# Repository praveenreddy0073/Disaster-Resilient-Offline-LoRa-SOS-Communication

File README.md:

# Earthquake Emergency SOS Communication System

## Overview

India experiences frequent earthquakes that can damage cellular towers and disrupt internet connectivity. During such emergencies, victims may be unable to communicate their location to rescue teams.

This project provides an infrastructure-independent emergency communication system using ESP32 and LoRa (SX1278) technology. The system enables users to transmit SOS alerts and GPS coordinates over long distances even when conventional communication networks fail.

## Problem Statement

During major earthquakes:

- Cellular towers may become unavailable
- Internet connectivity can be disrupted
- Victims cannot easily communicate their location
- Rescue teams face delays in locating survivors

This project addresses these challenges through a long-range wireless communication network.

## Proposed Solution

The system consists of:

Mobile App
↓
ESP32 User Node
↓
LoRa Communication
↓
Relay Node
↓
Base Station
↓
Rescue Team

The user sends an SOS request through a mobile application. The ESP32 User Node receives the request and forwards it using LoRa technology. Relay Nodes extend coverage and the Base Station receives the alert and displays victim information.

## Key Features

- Long-range communication up to 15 km (Line of Sight)
- GPS-based location sharing
- Infrastructure-independent operation
- Low-power communication
- Emergency SOS transmission
- Relay-based message forwarding
- Rescue acknowledgement system
- Disaster-resilient architecture

## Hardware Components

- ESP32 Development Board
- SX1278 LoRa Module (433 MHz)
- 433 MHz Antenna
- Mobile Device
- Power Supply

## Technologies Used

- ESP32
- LoRa (SX1278)
- Arduino IDE
- Firebase Studio
- Wi-Fi Communication
- GPS Location Services

## Why LoRa?

LoRa was selected because it offers:

- Long communication range
- Very low power consumption
- Strong signal penetration
- No dependency on cellular infrastructure
- Reliable communication in disaster environments

## Applications

- Earthquake Emergency Response
- Disaster Management
- Search and Rescue Operations
- Remote Area Communication
- Emergency Alert Systems

## Future Enhancements

- Automatic earthquake detection sensors
- Solar-powered relay stations
- Offline mapping support
- Multi-user communication network
- AI-based rescue prioritization

## Author

Praveen kumar
B.Tech Electronics and Communication Engineering
REVA University

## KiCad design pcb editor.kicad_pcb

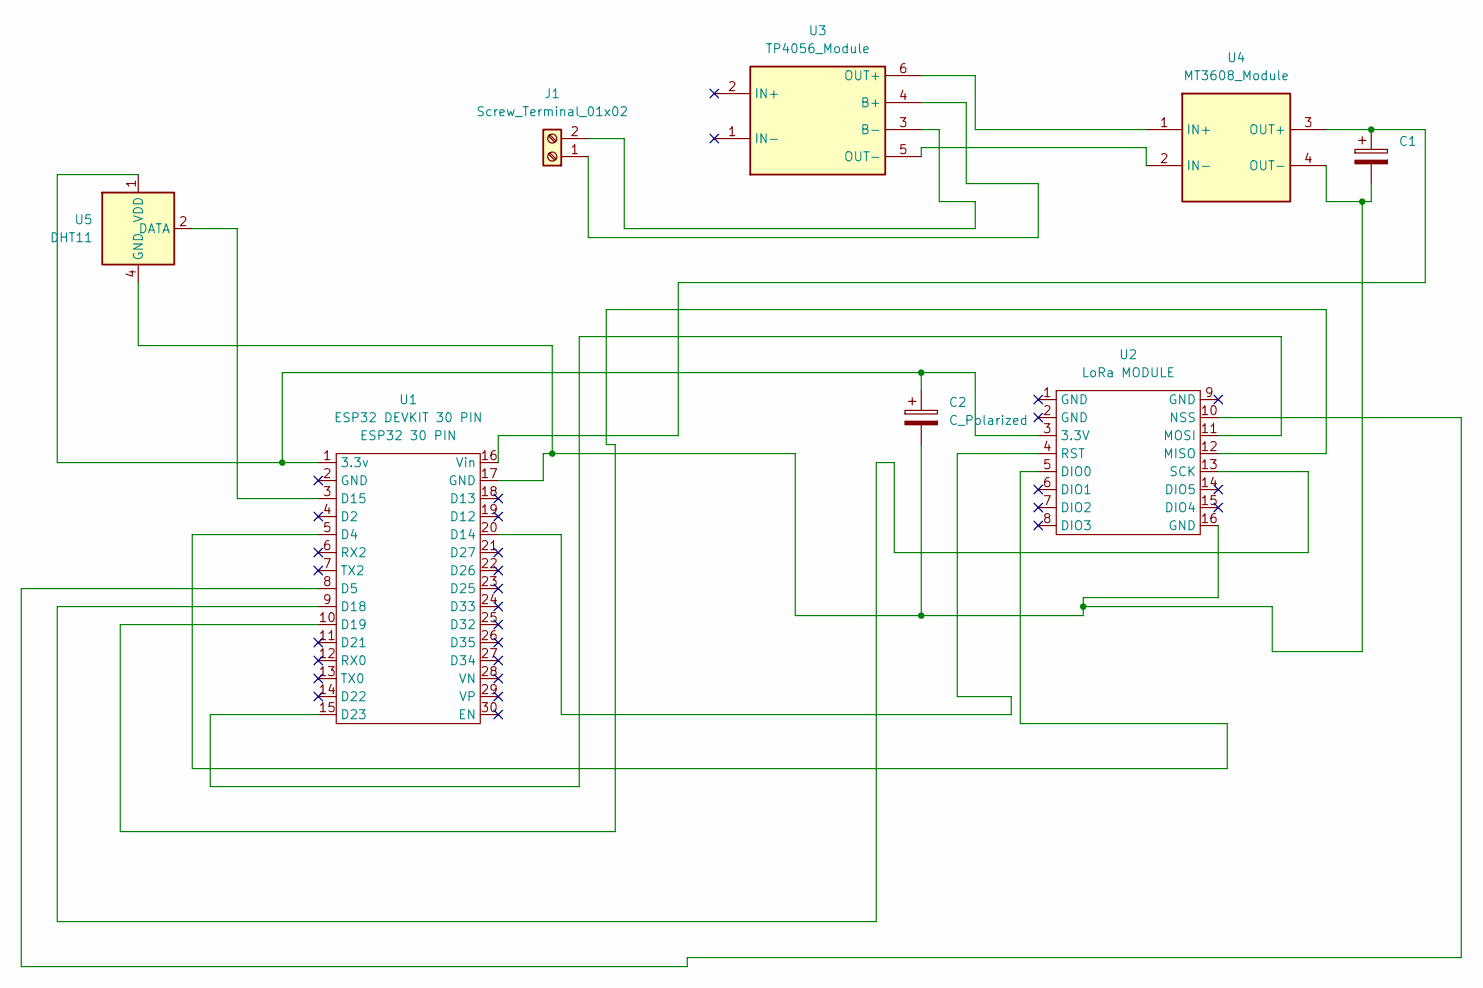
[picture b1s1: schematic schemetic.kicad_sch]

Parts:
C1: CP_Radial_D10.0mm_P5.00mm
C2: C_Polarized; CP_Radial_D10.0mm_P5.00mm
J1: Screw_Terminal_01x02; TerminalBlock_MaiXu_MX126-5.0-02P_1x02_P5.00mm
U1: ESP32 DEVKIT 30 PIN; ESP32 30 PIN
U2: LoRa MODULE; LORA MODULE
U3: TP4056_Module
U4: MT3608_Module
U5: DHT11; Aosong_DHT11_5.5x12.0_P2.54mm

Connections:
unnamed: J1.1, U3.4 (B+)
unnamed: J1.2, U3.3 (B-)
unnamed: C2.1, U1.1 (3.3v), U2.3 (3.3V), U5.1 (VDD)
unnamed: U1.5 (D4), U2.5 (DIO0)
unnamed: U1.8 (D5), U2.10 (NSS)
unnamed: U1.20 (D14), U2.4 (RST)
unnamed: U1.3 (D15), U5.2 (DATA)
unnamed: U1.9 (D18), U2.13 (SCK)
unnamed: U1.10 (D19), U2.12 (MISO)
unnamed: U1.15 (D23), U2.11 (MOSI)
unnamed: C1.1, U1.16 (Vin), U4.3 (OUT+)
unnamed: U3.6 (OUT+), U4.1 (IN+)
unnamed: U3.5 (OUT-), U4.2 (IN-)
unnamed: C1.2, C2.2, U1.17 (GND), U2.16 (GND), U4.4 (OUT-), U5.4 (GND)

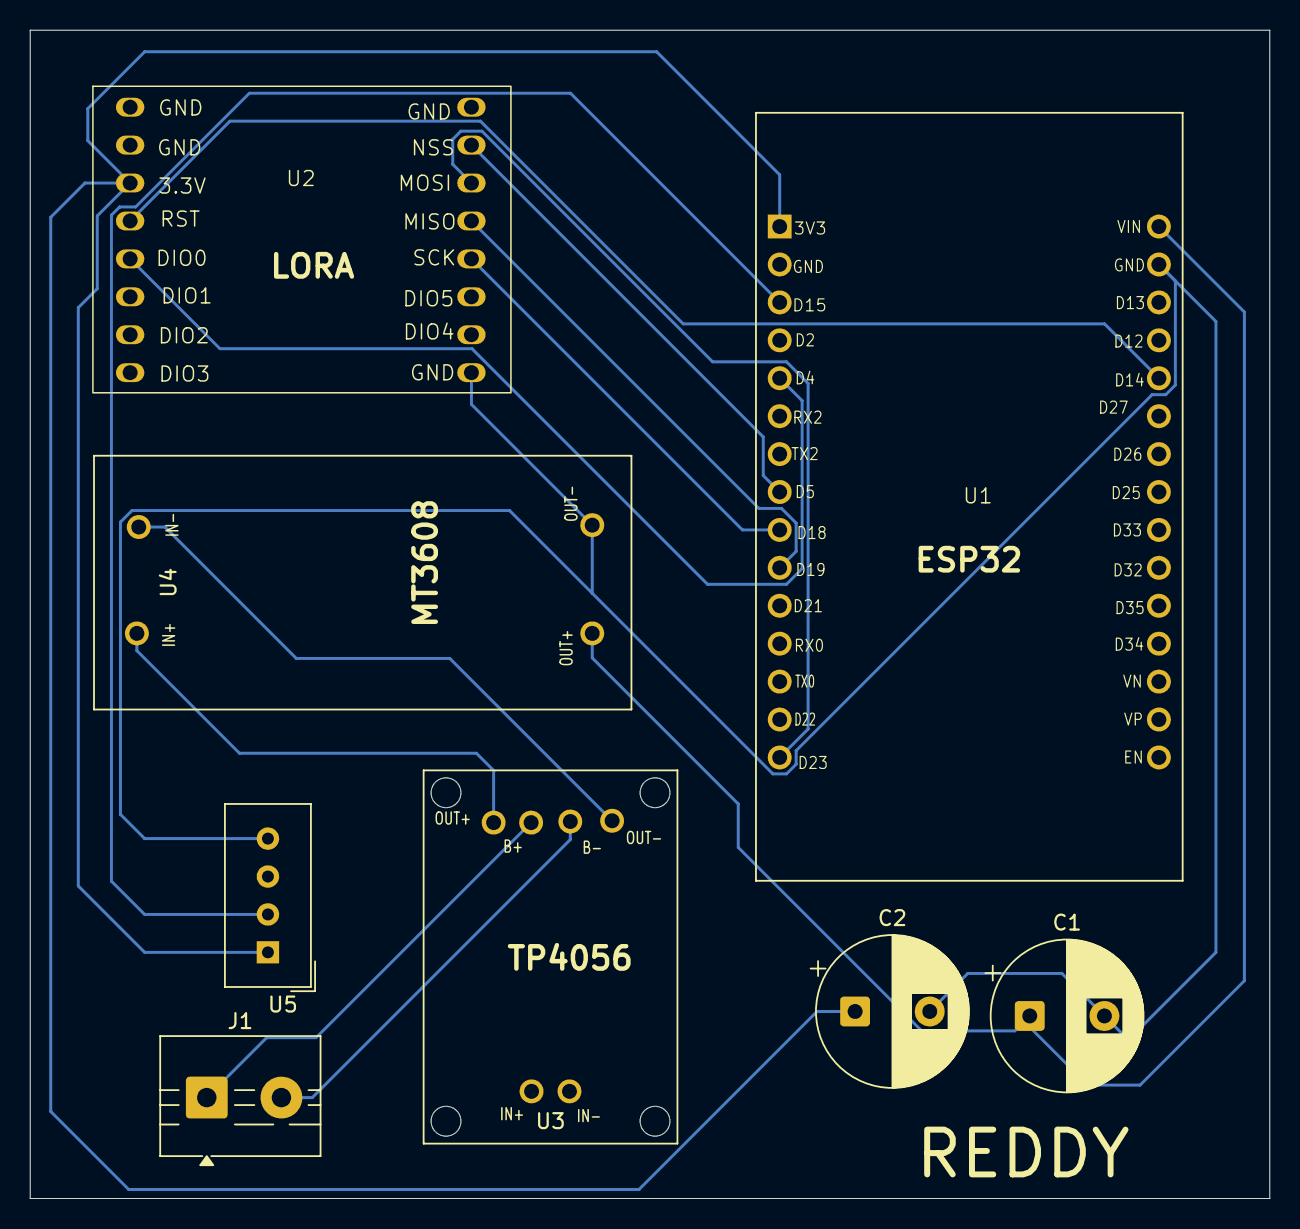
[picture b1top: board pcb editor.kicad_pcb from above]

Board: 2 copper layers, 83.0 x 78.2 mm, 8 parts (0 on the bottom side), 14 nets.
